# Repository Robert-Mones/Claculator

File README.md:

# Claculator
A reverse Polish notation calculator with added features such as comparisons, branching, and custom recursive operators taken from the Clac project from the 15-122 course at Carnegie Mellon University. The project is built around a 65C02 microprocessor with a custom architecture to reduce CPU load by making memory-mapped peripherals operate asynchronously. All logic and board design was done in KiCAD. All 3D modeling was done in Autodesk Fusion.

<p align="center">Fully assembled Claculator</p>

## Display
The seven-segment display board supports nine numeric displays, each with eight digits. It contains an SRAM chip which interfaces to the rest of the computer as a memory-mapped peripheral. When selected, the address and data bus is connected to the computer to be written to (but not read from) transparently. When the memory is not selected, a counter with a selectable clock source loops through each of the seventy-two digits, reads the corresponding byte from memory, and drives the corresponding digit using one bit for each segement (seven for the numeric part, one for the decimal point) with an array of P- and N-channel MOSFETs.

<p align="center">The front of the display, showing eight numeric displays</p>

<p align="center">The back of the display, showing the logic and driver chips</p>

## Keypad
The keypad input board supports up to sixteen rows (5 are implemented), each with eight buttons. It detects rising edges of each button (equivalent to KeyDown events) with hardware RC debouncing and writes this information to a hardware FIFO buffer which is interfaced directly to the address and data bus of the system and can be configured to send an interrupt on new information in the buffer. It also has a header and location for a seven-segment display (not populated in these photos) as the ninth display that is driven from the display board.

<p align="center">The front of the keypad, showing five groups of eight keys</p>

<p align="center">The back of the keypad, showing the logic chips and hot-swappable key sockets</p>

## Chassis
The chassis for the Claculator was manufactured by SendCutSend out of 1/8"-thick 304 stainless steel (except for the keypad plate which must be 0.06" thick to fit the keys). It has hinges at the top back to open the Claculator from the front to enable demonstrations and debugging more easily. It is very heavy (8lbs of sheet metal) and was very expensive but it's worth it for the bit.

<p align="center">Model of the assembled Claculator</p>

## Code
I am currently working on some tests building up to a 32-bit integer mode to develop the RPN behavior and a feature-complete Clac implementation. After this, I will write a software 32-bit floating point implementation to support decimal arithmetic and comparisons. All of the code for this project will be written in 65C02 assembly.

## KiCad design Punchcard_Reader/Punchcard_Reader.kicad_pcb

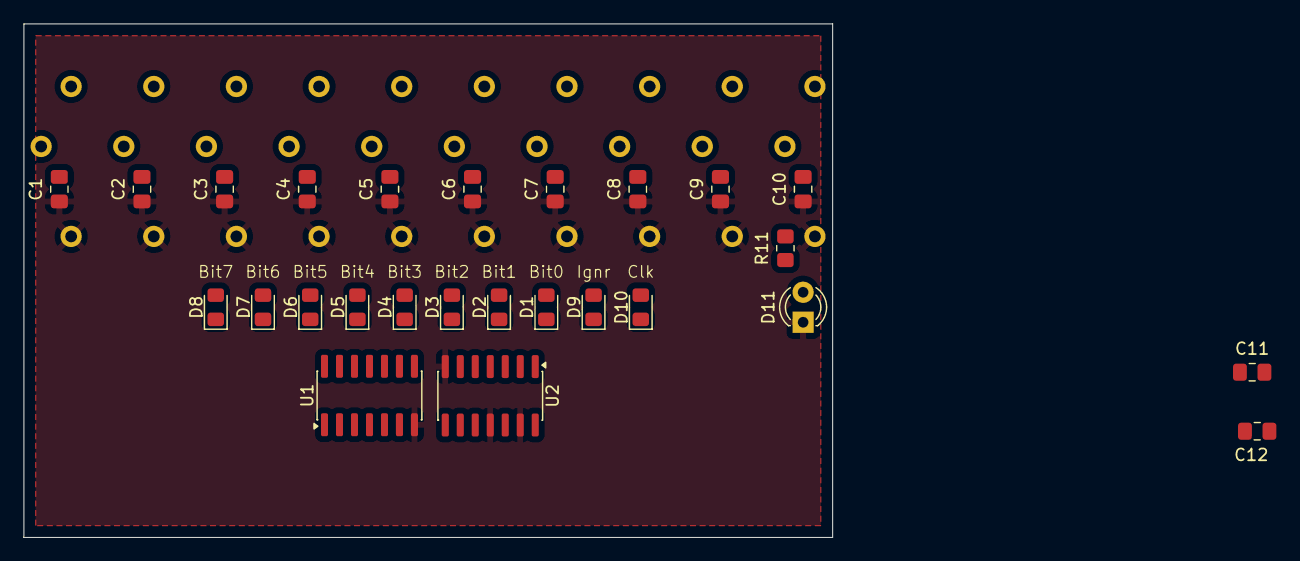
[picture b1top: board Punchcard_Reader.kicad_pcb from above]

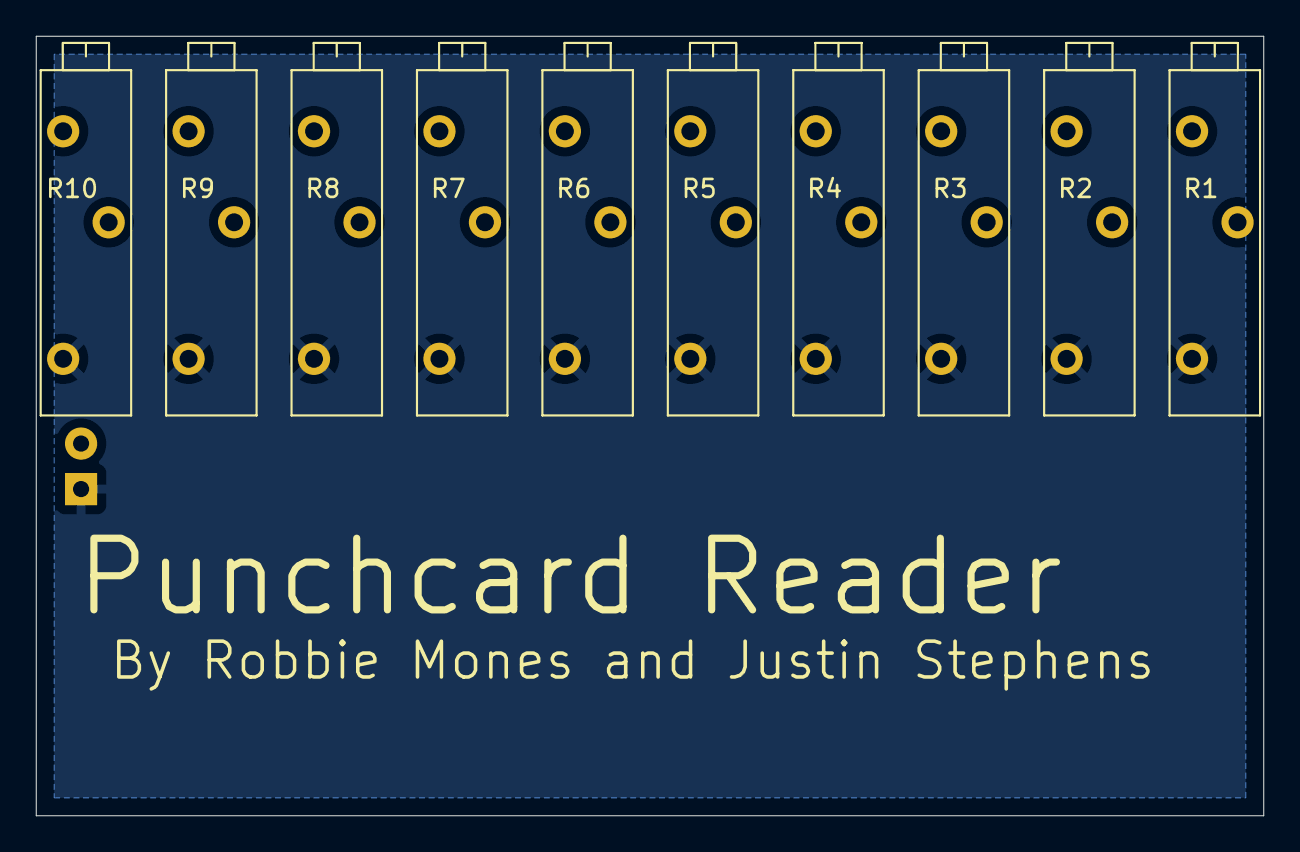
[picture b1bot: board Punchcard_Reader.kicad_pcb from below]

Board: 4 copper layers, 68.5 x 43.5 mm, 36 parts (10 on the bottom side), 13 nets, no tracks yet.

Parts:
C1, C2, C3, C4, C5, C6, C7, C8, C9, C10: 470pF; C_0805_2012Metric_Pad1.18x1.45mm_HandSolder
C11, C12: 0.1uF; C_0805_2012Metric_Pad1.18x1.45mm_HandSolder
D1, D2, D3, D4, D5, D6, D7, D8, D9, D10: APS2012SP1C; LED_0805_2012Metric_Pad1.15x1.40mm_HandSolder
D11: LED_BACKLIGHT; LED_D3.0mm
R1, R2, R3, R4, R5, R6, R7, R8, R9, R10: 500k; VariableResistor_Bourns_3006P_Horizontal_
R11: 120Ω; R_0805_2012Metric_Pad1.20x1.40mm_HandSolder
U1, U2: 74HC14; SOIC-14_3.9x8.7mm_P1.27mm

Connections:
+5V: C11.1, C12.1, D1.1 (K), D2.1 (K), D3.1 (K), D4.1 (K), D5.1 (K), D6.1 (K), D7.1 (K), D8.1 (K), D9.1 (K), D10.1 (K), R11.1, U1.14 (VCC), U2.14 (VCC)
GND: C1.2, C2.2, C3.2, C4.2, C5.2, C6.2, C7.2, C8.2, C9.2, C10.2, C11.2, C12.2, D11.1 (K), R1.1, R2.1, R3.1, R4.1, R5.1, R6.1, R7.1, R8.1, R9.1, R10.1, U1.7 (GND), U2.7 (GND), U2.11, U2.13
unnamed: C1.1, D1.2 (A), R1.2, U1.1
unnamed: C2.1, D2.2 (A), R2.2, U1.3
unnamed: C3.1, D3.2 (A), R3.2, U1.5
unnamed: C4.1, D4.2 (A), R4.2, U1.9
unnamed: C5.1, D5.2 (A), R5.2, U1.11
unnamed: C6.1, D6.2 (A), R6.2, U1.13
unnamed: C7.1, D7.2 (A), R7.2, U2.1
unnamed: C8.1, D8.2 (A), R8.2, U2.3
unnamed: C9.1, D9.2 (A), R9.2, U2.5
unnamed: C10.1, D10.2 (A), R10.2, U2.9
unnamed: D11.2 (A), R11.2

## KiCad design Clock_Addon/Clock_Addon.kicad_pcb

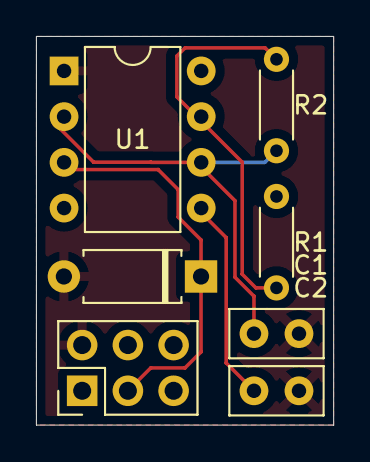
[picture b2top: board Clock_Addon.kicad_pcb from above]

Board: 6 copper layers, 16.5 x 21.6 mm, 7 parts (0 on the bottom side), 6 nets.

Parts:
C1, C2: C; C_Disc_D5.0mm_W2.5mm_P2.50mm
D1: D_Zener; D_A-405_P7.62mm_Horizontal
J2: Conn_01x06_Pin; PinHeader_2x03_P2.54mm_Vertical
R1, R2: R; R_Axial_DIN0204_L3.6mm_D1.6mm_P5.08mm_Horizontal
U1: NE555P; DIP-8_W7.62mm

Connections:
+5V: J2.1, R1.1, U1.4 (R), U1.8 (VCC)
CNTR_CLK: D1.1 (K), J2.3, U1.3 (Q)
GND: C1.2, C2.1, D1.2 (A), J2.2, U1.1 (GND)
unnamed: C2.2, U1.5 (CV)
unnamed: R1.2, R2.1, U1.7 (DIS)
unnamed: C1.1, R2.2, U1.2 (TR), U1.6 (THR)

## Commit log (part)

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2024-09-10 Added existing KiCAD projects
2026-01-06 Added kicad backups to gitignore
2026-01-06 Deleted old backups
2026-01-06 Added Clock_Addon kicad backups to gitignore
2026-01-06 Not sure
2026-01-06 Added Punchcard_Reader kicad backups and lock files to gitignore
2026-01-06 Punchcard_Reader init commit
2026-01-07 Added initial parts
2026-03-24 Added Keypad images and README info
2026-03-24 Added debugger submodule and current code
2026-03-27 Added DASM submodule
2026-03-27 Finished shl, shr and mul_fast
2026-03-28 Removed op_mul
2026-03-30 Added image of the real thing
2026-05-31 Working division
2026-05-31 Working mod
2026-05-31 Updated memory map
2026-06-25 Updated clac_test with new address decoding
2026-06-25 Added image of fully assembled Claculator
2026-06-27 Copied hardware test functionality into clac_int and made div and mod into single divmod op
2026-06-28 Implemented rendering
2026-06-28 Working numerical entry but horrifically slow
2026-06-28 Fixed entry of negative numbers
2026-06-29 Implemented double dabble rendering (much faster and correct for int_min)
2026-06-30 Added stack push and drop
